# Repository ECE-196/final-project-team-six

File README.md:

# Lending a Hand

> Authors: [Purab Balani], [Aleksandar Jeremic], [Syler Sylvester]

## Problem Definition
> * Why is the problem you are trying to solve?

Over 1.3 billion people across the globe are afflicted with disabilities that make leading a normal life difficult compared to able-bodied people. More specifically, another arm or hand could make maneuvering around or reaching essentials much easier.

https://www.who.int/news-room/fact-sheets/detail/disability-and-health

> * What motivated you to solve the following problem?

What motivated us to solve this problem was a personal experience one of us had that deeply moved us. While shopping at the mall, there was a person with a disability struggling to open a door. This moment highlighted the everyday challenges faced by individuals with disabilities, particularly those who have lost an arm or have limited motor functions. It inspired us to create a solution that could make their lives easier and more independent. Our goal is to develop technology that can assist with basic motor functions, ultimately improving the quality of life for people with disabilities.

## Proposed Idea

Our proposed idea to alleviate some of the physical struggles experienced by individuals with disabilities, is a robotic arm that could be mounted in various places that can be used for performing basic tasks like picking up objects and opening cabinets.

(image of the proposed model goes here)

## Milestones
>* Design system and components list - A robust system will be designed to layout the component interaction and general structure of the arm (10/23)
> * CAD and print/cut the robot base, arms, and linkages (10/25)
> * R&D for PCB - We will need to research existing stepper motor drives to adapt onto our PCB to also include drives for our three servo motors and serial connection to our game controller (Week something)
> * Test components - After the design phase of our project we will shift to system integration which will start confirming our system design by testing that our components mesh with each other (Arrival of components)
> * Assemble arm - With confirmation of our components being viable for our use, we will assemble our full system with components and iterate to create final assembly (Week 7)
> * Calibrate arm - Map controller buttons and calibrate motor movements for smooth operations (Week 7)
> * Test robotic arm function - After initial calibration and assembly we will move onto testing our system to gauge its functionality and limitations along with tweaking the system for best performance (Week 8)

## Testable Hypothesis

> * How do you  plan on testing your proposed solution?

To test the effectiveness of our solution, we plan to demonstrate the ability of our robotic arm by picking up objects such as an apple or a water bottle along with demonstrating its effectiveness in aiding in opening a cabinet.

# Submission

1. All your work!

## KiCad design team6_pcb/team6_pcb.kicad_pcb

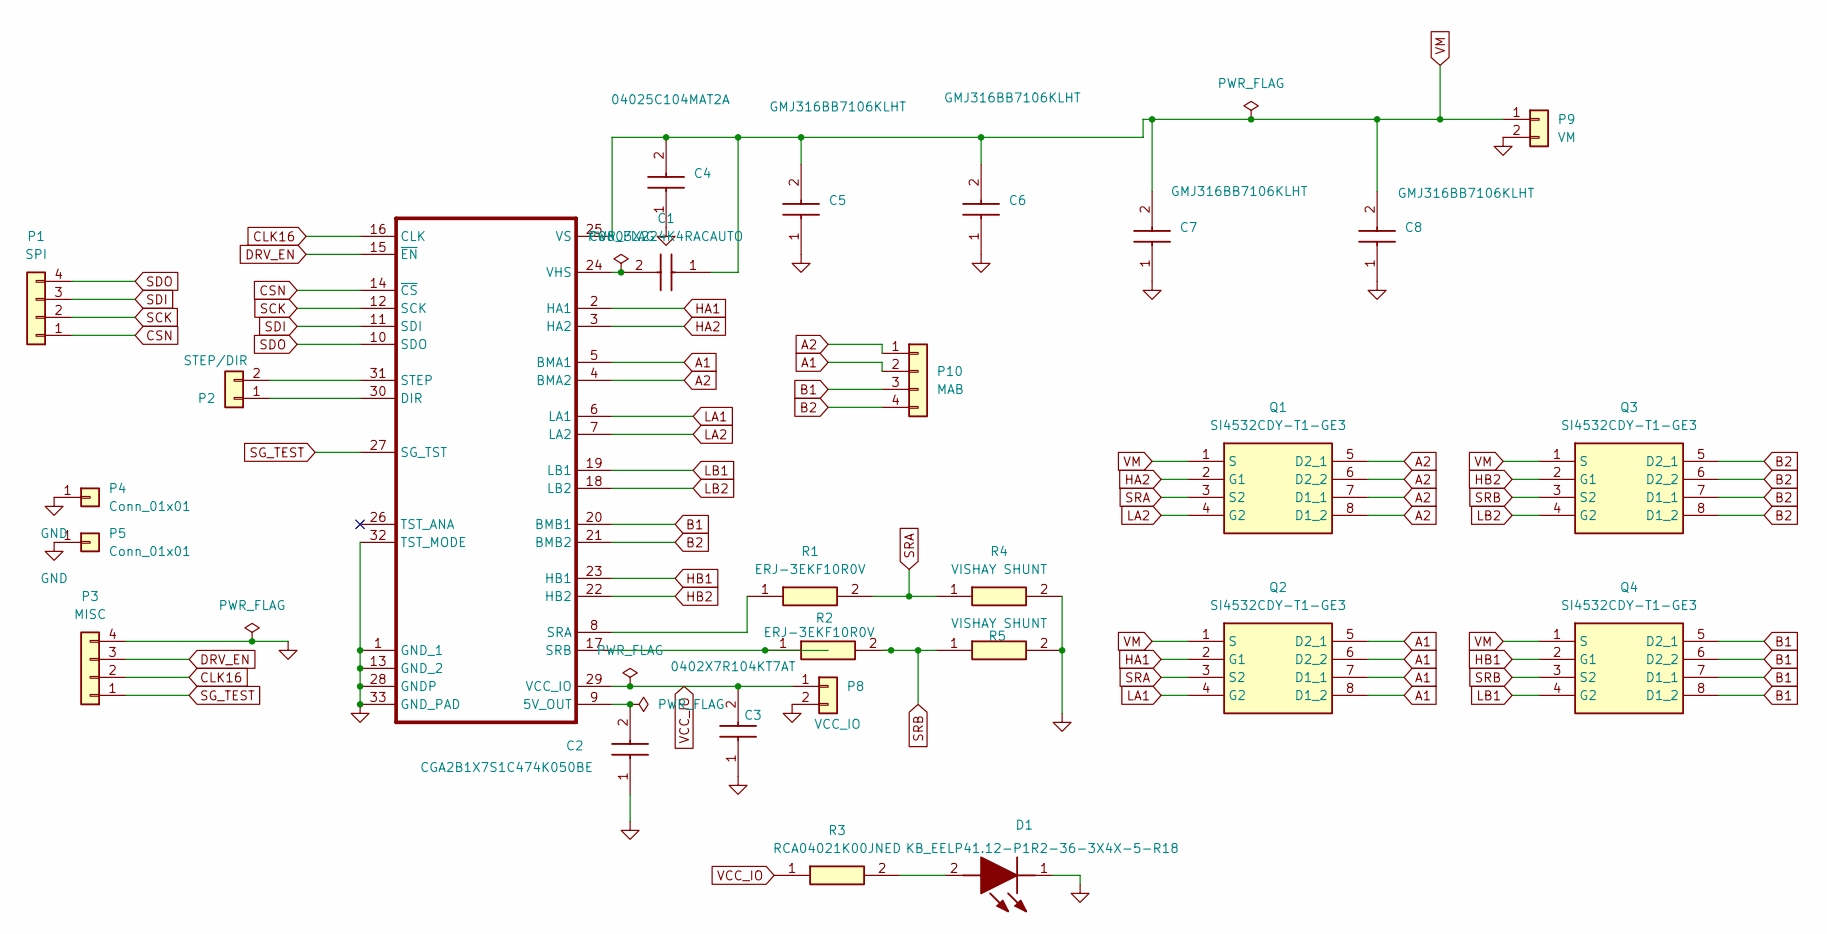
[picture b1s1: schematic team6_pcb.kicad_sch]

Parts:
C1: C0603X224K4RACAUTO; C_0603_1608Metric; Mouser Part Number 80-C0603X224K4RAUTO
C2: CGA2B1X7S1C474K050BE; C_0402_1005Metric; Mouser Part Number 810-CGA2B1X7S1C474KB
C3: 0402X7R104KT7AT; C_0402_1005Metric; Mouser Part Number 581-0402X7R104KT7AT
C4: 04025C104MAT2A; C_0402_1005Metric; Mouser Part Number 581-04025C104MAT2A
C5, C6, C7, C8: GMJ316BB7106KLHT; C_1206_3216Metric; Mouser Part Number 963-GMJ316BB7106KLHT
D1: KB_EELP41.12-P1R2-36-3X4X-5-R18; LED_0805_2012Metric; Mouser Part Number 720-P4112P1R2363X4X5
IC1: QFN-32-1EP_5x5mm_P0.5mm_EP3.3x3.3mm_ThermalVias
P1: SPI; PinHeader_1x04_P2.54mm_Vertical
P2: STEP/DIR; PinHeader_1x02_P2.54mm_Vertical
P3: MISC; PinHeader_1x04_P2.54mm_Vertical
P4, P5: Conn_01x01; PinHeader_1x01_P2.54mm_Vertical
P8: VCC_IO; PinHeader_1x02_P2.54mm_Vertical
P9: VM; PhoenixContact_MSTBA_2,5_2-G_1x02_P5.00mm_Horizontal
P10: MAB; PinHeader_1x04_P2.54mm_Vertical
Q1, Q2, Q3, Q4: SI4532CDY-T1-GE3; SOT127P600X175-8N; Mouser Part Number 781-SI4532CDY-GE3
R1, R2: ERJ-3EKF10R0V; R_0603_1608Metric; Mouser Part Number 71-WSR2R0500FEA
R3: RCA04021K00JNED; R_0402_1005Metric; Mouser Part Number 71-RCA04021K00JNED
R4, R5: VISHAY SHUNT; R_2512_6332Metric; Mouser Part Number 71-WFMB2010R0750FEA

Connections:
A1: IC1.5 (BMA1), P10.2, Q2.5 (D2_1), Q2.6 (D2_2), Q2.7 (D1_1), Q2.8 (D1_2)
A2: IC1.4 (BMA2), P10.1, Q1.5 (D2_1), Q1.6 (D2_2), Q1.7 (D1_1), Q1.8 (D1_2)
B1: IC1.20 (BMB1), P10.3, Q4.5 (D2_1), Q4.6 (D2_2), Q4.7 (D1_1), Q4.8 (D1_2)
B2: IC1.21 (BMB2), P10.4, Q3.5 (D2_1), Q3.6 (D2_2), Q3.7 (D1_1), Q3.8 (D1_2)
CLK16: IC1.16 (CLK), P3.2
CSN: IC1.14 (~CS), P1.1
DRV_EN: IC1.15 (~EN), P3.3
GND: C2.1, C3.1, C4.1, C5.1, C6.1, C7.1, C8.1, D1.1 (K), IC1.1 (GND_1), IC1.13 (GND_2), IC1.28 (GNDP), IC1.32 (TST_MODE), IC1.33 (GND_PAD), P3.4, P4.1, P5.1, P8.2, P9.2, R4.2, R5.2
HA1: IC1.2 (HA1), Q2.2 (G1)
HA2: IC1.3 (HA2), Q1.2 (G1)
HB1: IC1.23 (HB1), Q4.2 (G1)
HB2: IC1.22 (HB2), Q3.2 (G1)
LA1: IC1.6 (LA1), Q2.4 (G2)
LA2: IC1.7 (LA2), Q1.4 (G2)
LB1: IC1.19 (LB1), Q4.4 (G2)
LB2: IC1.18 (LB2), Q3.4 (G2)
unnamed: D1.2 (A), R3.2
unnamed: C2.2, IC1.9 (5V_OUT)
unnamed: IC1.30 (DIR), P2.1
unnamed: IC1.8 (SRA), R1.1
unnamed: IC1.17 (SRB), R2.1
unnamed: IC1.31 (STEP), P2.2
unnamed: C1.2, IC1.24 (VHS)
SCK: IC1.12 (SCK), P1.2
SDI: IC1.11 (SDI), P1.3
SDO: IC1.10 (SDO), P1.4
SG_TEST: IC1.27 (SG_TST), P3.1
SRA: Q1.3 (S2), Q2.3 (S2), R1.2, R4.1
SRB: Q3.3 (S2), Q4.3 (S2), R2.2, R5.1
VCC_IO: C3.2, IC1.29 (VCC_IO), P8.1, R3.1
VM: C1.1, C4.2, C5.2, C6.2, C7.2, C8.2, IC1.25 (VS), P9.1, Q1.1 (S), Q2.1 (S), Q3.1 (S), Q4.1 (S)

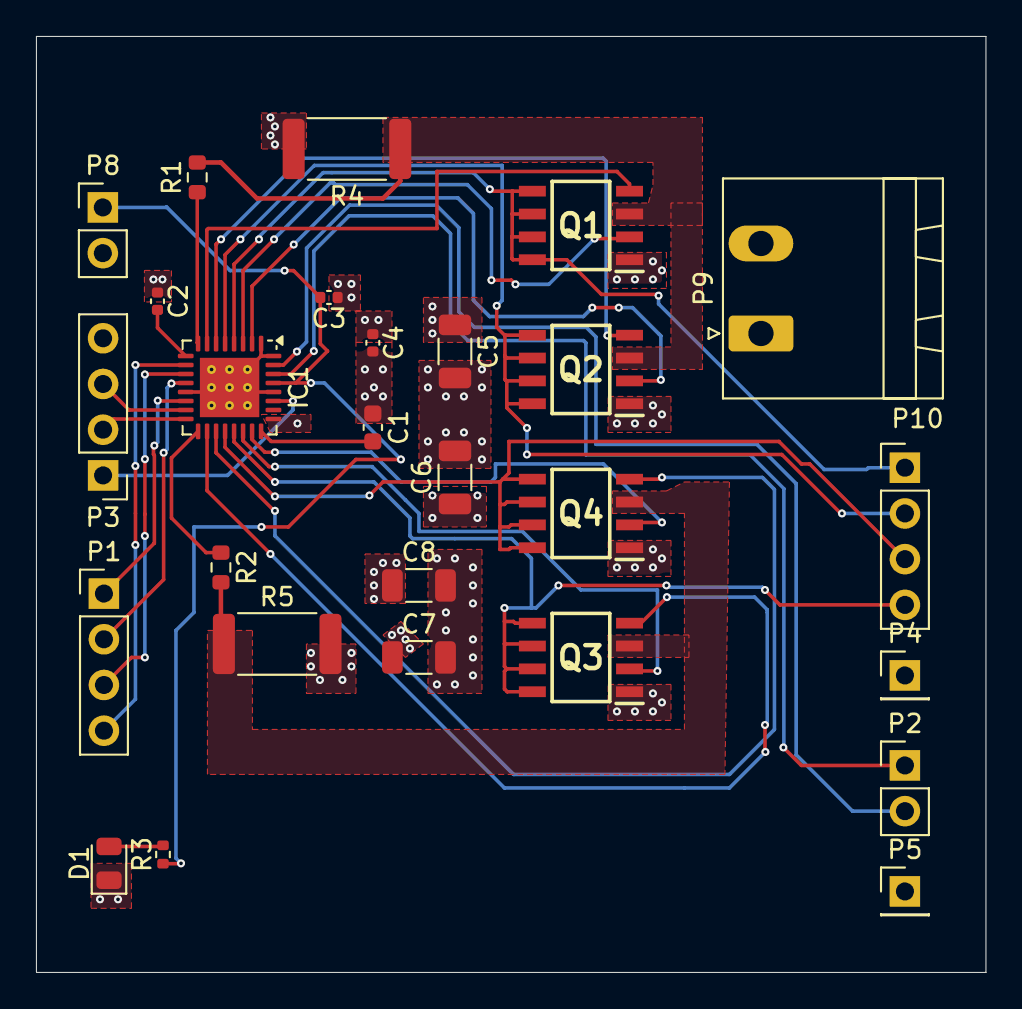
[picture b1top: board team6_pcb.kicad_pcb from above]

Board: 4 copper layers, 52.8 x 52.0 mm, 27 parts (0 on the bottom side), 31 nets.

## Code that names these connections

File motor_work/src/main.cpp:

#include <SPI.h>
#include <Arduino.h>
#include "TMC262.c"

// Define the SPI pins
#define TMC_MISO 1  // SDO -> MISO on ESP32
#define TMC_MOSI 2  // SDI -> MOSI on ESP32
#define TMC_SCK  3// SCK -> SCK on ESP32
#define TMC_CS   4   // CSN -> CS/SS on ESP32

#define STEP_PIN 5   // GPIO for STEP
#define DIR_PIN  6   // GPIO for DIR

const int stepCount = 50;  // Number of steps for a small move
const int stepDelay = 500; // Delay in microseconds (controls speed)

void setup() {
  // Initialize SPI with custom pins
  SPI.begin(TMC_SCK, TMC_MISO, TMC_MOSI, TMC_CS);
  
  // Configure Step/Dir pins
  pinMode(STEP_PIN, OUTPUT);
  pinMode(DIR_PIN, OUTPUT);

  // Set default direction
  digitalWrite(DIR_PIN, HIGH); // Set direction to forward

  // Initialize the TMC262
  tmc262_initMotorDrivers();

  // Configure TMC262 settings (example: 16 microsteps)
  tmc262_setStepDirMStepRes(4); // 16 microsteps
  tmc262_setStepDirInterpolation(1); // Enable interpolation
}

void loop() {
  // Move the motor a small amount
  moveMotor(stepCount, stepDelay);

  // Wait a bit
  delay(1000);

  // Change direction and move back
  digitalWrite(DIR_PIN, LOW); // Reverse direction
  moveMotor(stepCount, stepDelay);

  // Wait again
  delay(1000);
}
void moveMotor(int steps, int delayMicroseconds) {
  for (int i = 0; i < steps; i++) {
    digitalWrite(STEP_PIN, HIGH); // Step pulse HIGH
    delayMicroseconds(delayMicroseconds); // Short delay
    digitalWrite(STEP_PIN, LOW);  // Step pulse LOW
    delayMicroseconds(delayMicroseconds); // Short delay
  }
}

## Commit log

2024-10-29 PCB base design
2024-10-29 working on some stuff
2024-10-29 created CAD folder and andded base design
2024-10-29 added folder for STL
2024-10-30 this is alot
    good luck
2024-10-30 here it is to be renamed
    here we go
2024-10-30 team6_pcb_schematic
    Legit
2024-10-30 actual schematic
2024-10-31 PCB for ming
2024-10-31 Removal
2024-10-31 team6_project
2024-10-31 team6_final_sumbits
    Adin Stamped
2024-10-31 Gerber Files
2024-11-23 motor work dir
2024-12-01 ESPNOW send -Purab
2024-12-01 recieve wireless -Purab
2024-12-01 working code for grabber with bluetooth control
2024-12-03 Create controlAllMotors.ino -Purab
2024-12-03 need to change pins, direction, and measurements
2024-12-03 cleaned github
